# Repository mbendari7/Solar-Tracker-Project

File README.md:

# Solar Tracker Project

An active solar tracking system designed to optimize photovoltaic energy collection by continuously aligning solar panels with the most intense light source. This repository contains the complete project files, including custom PCB schematics, C++ firmware, and 3D-printable mechanical assemblies. 

The system utilizes closed-loop control, reading environmental light gradients through an array of sensors and actuating motors to maintain optimal panel orientation.

## Project Architecture

The project is divided into three main engineering domains: electrical hardware, mechanical design, and embedded firmware. 

### 1. Hardware and Electronics
The circuit design and PCB layouts were developed using KiCad. The hardware system is responsible for signal acquisition and motor power distribution.

*   **Microcontroller:** Arduino-compatible MCU for processing ADC readings and generating PWM control signals.
*   **Sensors:** Light Dependent Resistors (LDRs) arranged in a directional array with voltage divider networks to measure horizontal and vertical light differentials.
*   **Actuators:** Servos (or stepper motors) to control the pan (azimuth) and tilt (elevation) axes.
*   **Power Management:** Isolated power routing to prevent motor current spikes from inducing noise or brownouts on the logic circuit.
*   **Design Files:** Schematics, PCB layouts, and Gerber files are located in the `hardware/` directory.

### 2. Embedded Firmware
The control logic is written entirely in C++ and focuses on efficiency and preventing mechanical jitter. 

*   **Platform:** C++ (compiled via Arduino IDE or PlatformIO).
*   **Control Loop:** The firmware continuously polls the analog pins connected to the LDRs, calculates the light differential across the axes, and updates motor positions accordingly.
*   **Hysteresis Implementation:** A software-defined deadband is included to filter out minor lighting fluctuations (like passing clouds or sensor noise). This prevents continuous, unnecessary motor twitching, which saves power and reduces mechanical wear.
*   **Source Files:** All code, including headers and main operational logic, can be found in the `firmware/` directory.

### 3. Mechanical Design
The physical chassis is custom-designed for structural rigidity and minimal weight, ensuring the motors do not experience excessive torque loads. 

*   **Fabrication:** Designed for Fused Deposition Modeling (FDM) 3D printing. PLA or PETG is recommended for durability.
*   **Components:** Includes the base mount, azimuth rotation brackets, elevation tilt brackets, and the solar panel mounting plate. A cross-shaped LDR shadow shield is also included to cast distinct shadows over the sensors when the panel is not perfectly aligned.
*   **CAD Files:** STL files and step files are provided in the `cad/` directory.

## Repository Structure

├── cad/                  # 3D printable models (.STL files for chassis and mounts)
├── hardware/             # KiCad schematic files, PCB layouts, and gerbers
├── firmware/             # C++ source code for the microcontroller
├── docs/                 # Wiring diagrams and supplemental documentation
└── README.md             # Project overview

## Setup and Assembly

### Mechanical Assembly
1. Print all components located in the `cad/` directory with a minimum of 20% infill for structural integrity.
2. Assemble the base and mount the azimuth motor.
3. Attach the elevation bracket and corresponding motor.
4. Mount the LDR array and attach the cross-shield to ensure accurate differential shading.

### Electronics Wiring
1. Open the KiCad schematics in the `hardware/` folder to review the pinout.
2. Wire the LDR voltage dividers to the analog input pins of your MCU.
3. Connect the motor control lines to the designated PWM output pins.
4. Ensure the motors are powered by an adequate external power supply with a common ground shared with the MCU.

### Firmware Flashing
1. Open the `firmware/` directory in your preferred IDE.
2. Verify that the assigned pin definitions in the header files match your physical wiring.
3. Adjust the threshold and delay variables if your specific ambient lighting environment requires more or less sensitivity.
4. Compile and upload the code to the microcontroller.

## Future Improvements

*   Implementation of real-time clock (RTC) modules for predictive solar tracking based on time of day and geographical coordinates.
*   Integration of current and voltage sensors to log actual power generation data.
*   Migrating from servo motors to precision stepper motors for larger panel handling.

## License

This project is open-source. Feel free to fork the repository, submit pull requests, or adapt the designs for your own applications.

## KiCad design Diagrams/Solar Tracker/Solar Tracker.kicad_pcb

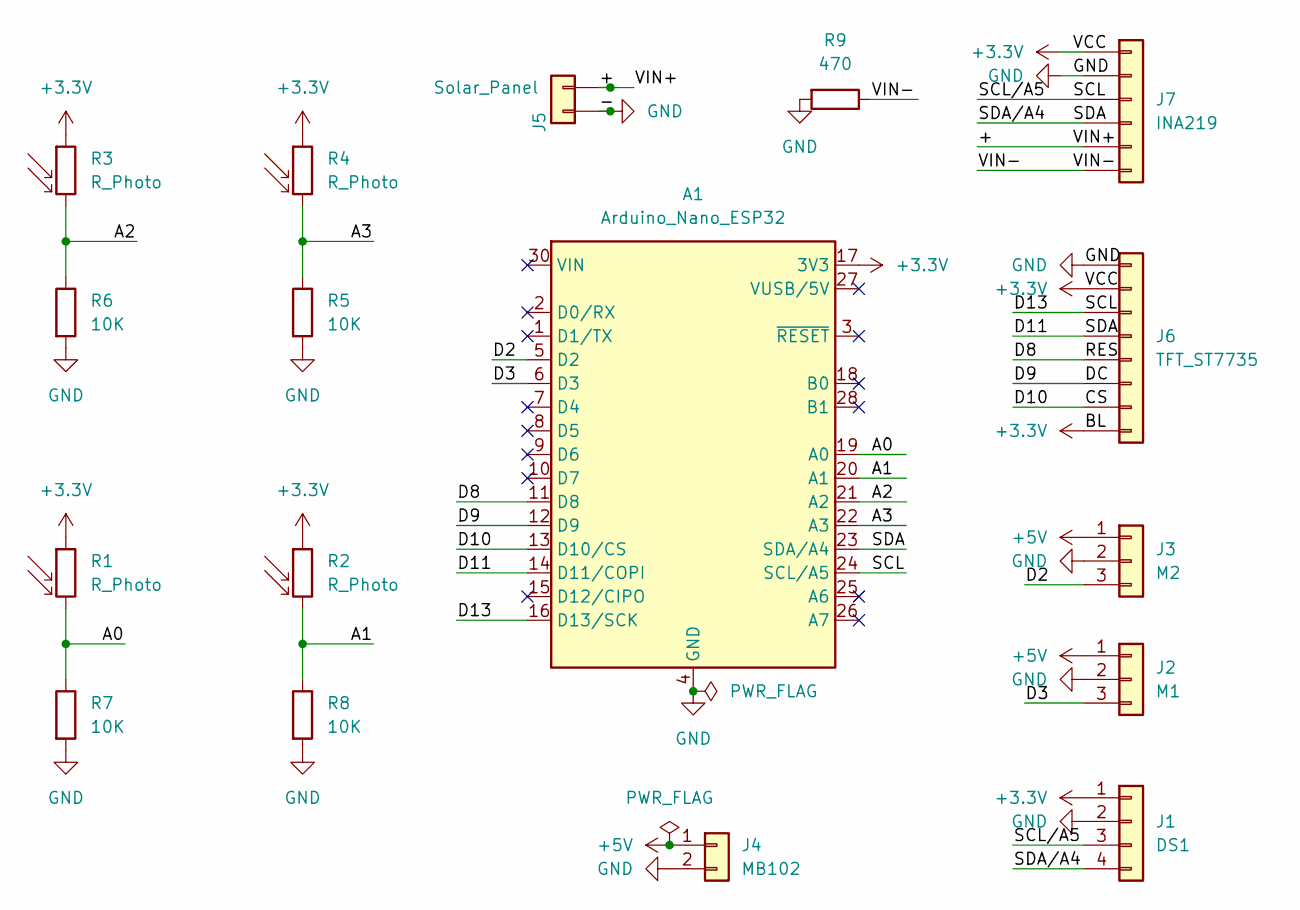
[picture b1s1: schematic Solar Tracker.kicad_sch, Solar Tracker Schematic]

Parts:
A1: Arduino_Nano_ESP32; Arduino_Nano
J1: DS1; PinHeader_1x04_P2.54mm_Vertical
J2: M1; PinHeader_1x03_P2.54mm_Vertical
J3: M2; PinHeader_1x03_P2.54mm_Vertical
J4: MB102; TerminalBlock_Phoenix_MKDS-1,5-2-5.08_1x02_P5.08mm_Horizont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
J5: Solar_Panel; TerminalBlock_Phoenix_MKDS-1,5-2-5.08_1x02_P5.08mm_Horizont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
J6: TFT_ST7735; PinHeader_1x08_P2.54mm_Vertical
J7: INA219; PinHeader_1x06_P2.54mm_Vertical
R1, R2, R3, R4: R_Photo; R_LDR_5.1x4.3mm_P3.4mm_Vertical
R5, R6, R7, R8: 10K; R_Axial_DIN0207_L6.3mm_D2.5mm_P10.16mm_Horizontal
R9: 470; R_Axial_DIN0207_L6.3mm_D2.5mm_P10.16mm_Horizontal

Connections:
+3.3V: A1.17 (3V3), J1.1, J6.2, J6.8, J7.1, R1.1, R2.1, R3.1, R4.1
+5V: J2.1, J3.1, J4.1
/+: J5.2, J7.5
/A0: A1.19 (A0), R1.2, R7.1
/A1: A1.20 (A1), R2.2, R8.1
/A2: A1.21 (A2), R3.2, R6.1
/A3: A1.22 (A3), R4.2, R5.1
/CS: A1.13 (D10/CS), J6.7
/D2: A1.5 (D2), J3.3
/D3: A1.6 (D3), J2.3
/D8: A1.11 (D8), J6.5
/D9: A1.12 (D9), J6.6
/D11: A1.14 (D11/COPI), A1.23 (SDA/A4), J1.4, J6.4, J7.4
/D13: A1.16 (D13/SCK), A1.24 (SCL/A5), J1.3, J6.3, J7.3
/VIN-: J7.6, R9.1
GND: A1.4 (GND), A1.29 (GND), J1.2, J2.2, J3.2, J4.2, J5.1, J6.1, J7.2, R5.2, R6.2, R7.2, R8.2, R9.2

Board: 2 copper layers, 17 parts (0 on the bottom side), 16 nets, no tracks yet.

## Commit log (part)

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2026-06-08 Created PlatformIO and edited it
    Editied the platformio.ini file to my specific platform of arduino nano esp32. Added screen and servo libraries as well.
2026-06-10 Add visual circuit diagram image
    Added image of a visual rough idea of the circuit
2026-06-11 Add Solar Tracker KiCad project files
    Add a new KiCad project 'Solar Tracker' under Diagrams/Solar Tracker. This commit introduces the schematic (.kicad_sch), PCB file (.kicad_pcb), project settings and preferences (.kicad_pro, .kicad_pr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
2026-06-11 Added Kicad PDF
    Added a PDF of the schematic.
2026-06-11 Clean up extra files
2026-06-11 Move PlatformIO files; add solar-tracker sketch
    Rename/move PlatformIO project files to repo root (.gitignore, .vscode/extensions.json, include/, lib/, platformio.ini, test/README) and remove the old placeholder PlatformIO/src/main.cpp. Add a new 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
2026-06-12 Updated the Solar Tracker Schematic
2026-06-12 Updated SCH file for circuit and Netwired it
2026-06-13 Update Solar Tracker schematic & project files
    Add updated screen module PDF and apply multiple KiCad project/schematic updates. Changes include updating used_designators in the .kicad_pro, adding a generic 1x08 connector symbol and many schemati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
2026-06-16 Add CAD/STEP/STL for solar_tracker_ALL
    Add full CAD exports and mesh for the solar_tracker_ALL model: SolidWorks assembly (.SLDASM), STEP (.step) and STL (.stl) placed under 'CAD and STL/'. STEP file was exported via Open CASCADE and incl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
2026-06-16 Updated Code with Wireless Network
2026-06-16 Refactor and document solar tracker firmware
    Reorganise and enrich the main firmware: expand and clarify the file header and wiring notes; add detailed comments for hardware, networking, runtime variables and web dashboard behavior; define and 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
2026-06-18 Add DFU upload and serial startup delay
    platformio.ini: set upload_protocol to dfu and monitor_port to COM5 to use DFU uploads and target the serial monitor port. src/main.cpp: add a 3s delay after Serial.begin and print a "Booting up..." 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
